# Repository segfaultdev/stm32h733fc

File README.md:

# STM32H733VGT6 Flight Controller

## Overview

This repository contains the hardware documentation and pinout routing for a custom flight controller based on the STM32H733VGT6 microcontroller. Designed for high-performance flight dynamics, this board leverages the MCU's 550 MHz clock speed, math coprocessor, and extensive I/O capabilities.

---

## Current Pinout & Peripheral Mapping

Below is the structured peripheral documentation based on the current schematic routing.

### 1. Serial Peripheral Interface (SPI)

*Primarily used for high-speed sensors (IMU), OSD chips, Blackbox Flash memory, and SD Cards.*

| Peripheral     | Pins              | Typical Signal Mapping                           | Suggested Use Case                                 |
| :------------- | :---------------- | :----------------------------------------------- | :------------------------------------------------- |
| **SPI1** | PA4 - PA7         | PA4 (NSS), PA5 (SCK), PA6 (MISO), PA7 (MOSI)     | **Primary IMU** (e.g., MPU6000, BMI270)      |
| **SPI2** | PB12 - PB15       | PB12 (NSS), PB13 (SCK), PB14 (MISO), PB15 (MOSI) | **Secondary IMU** or **OSD** (AT7456E) |
| **SPI3** | PA15, PC10 - PC12 | PA15 (NSS), PC10 (SCK), PC11 (MISO), PC12 (MOSI) | **Blackbox Flash** (e.g., W25Q128)           |
| **SPI4** | PE11 - PE14       | PE11 (NSS), PE12 (SCK), PE13 (MISO), PE14 (MOSI) | **SD Card** or **Third IMU**           |

### 2. Inter-Integrated Circuit (I2C)

*Used for slower, address-based peripherals like Barometers and Compasses.*

| Peripheral     | Pins        | Signal Mapping         | Suggested Use Case                             |
| :------------- | :---------- | :--------------------- | :--------------------------------------------- |
| **I2C1** | PB6 - PB7   | PB6 (SCL), PB7 (SDA)   | **Barometer** (e.g., BMP280, DPS310)     |
| **I2C2** | PB10 - PB11 | PB10 (SCL), PB11 (SDA) | **Magnetometer/Compass** (e.g., QMC5883) |
| **I2C4** | PD12 - PD13 | PD12 (SCL), PD13 (SDA) | Breakout / I2C Expansion Pad                   |

### 3. Universal Asynchronous Receiver-Transmitter (UART)

*Used for external communications: Radio Receivers, GPS, Digital Video Transmitters, and Telemetry.*

| Peripheral       | Pins        | Signal Mapping       | Suggested Use Case                                |
| :--------------- | :---------- | :------------------- | :------------------------------------------------ |
| **UART1**  | PA9 - PA10  | PA9 (TX), PA10 (RX)  | **Digital VTX** (DJI O3, Walksnail, HDZero) |
| **UART2**  | PA2 - PA3   | PA2 (TX), PA3 (RX)   | **Radio Receiver** (ExpressLRS / Crossfire) |
| **UART3**  | PD8 - PD9   | PD8 (TX), PD9 (RX)   | **GPS** (RX to GPS TX, TX to GPS RX)        |
| **UART4**  | PA0 - PA1   | PA0 (TX), PA1 (RX)   | **ESC Telemetry** (Usually RX only needed)  |
| **UART7**  | PE7 - PE8   | PE8 (TX), PE7 (RX)   | Free Serial Port                                  |
| **UART8**  | PE0 - PE1   | PE1 (TX), PE0 (RX)   | Free Serial Port                                  |
| **UART9**  | PD14 - PD15 | PD15 (TX), PD14 (RX) | Free Serial Port                                  |
| **UART10** | PE2 - PE3   | PE3 (TX), PE2 (RX)   | Free Serial Port                                  |

### 4. Controller Area Network (CAN)

*Used for robust, high-speed communication with DroneCAN peripherals (smart ESCs, advanced GPS modules).*

| Peripheral       | Pins      | Signal Mapping     | Suggested Use Case                |
| :--------------- | :-------- | :----------------- | :-------------------------------- |
| **FDCAN1** | PB8 - PB9 | PB9 (TX), PB8 (RX) | **DroneCAN Peripheral Bus** |

### 5. Timers & Motor Outputs

*Used for sending DSHOT or PWM signals to the Electronic Speed Controllers (ESCs).*

| Peripheral     | Pins      | Signal Mapping                             | Suggested Use Case                      |
| :------------- | :-------- | :----------------------------------------- | :-------------------------------------- |
| **TIM8** | PC6 - PC9 | PC6 (CH1), PC7 (CH2), PC8 (CH3), PC9 (CH4) | **Motor 1-4 Outputs** (DSHOT/PWM) |

---

## Hardware Routing To-Do List

The following critical subsystems still need to be established to make the flight controller fully functional.

- [ ] **USB Communication:** Route `PA11` (USB_D-) and `PA12` (USB_D+) and design the USB-C connector circuit with 5.1k CC pull-down resistors.
- [ ] **Debug and Flashing (SWD):** Route `PA13` (SWDIO) and `PA14` (SWCLK) to dedicated debug pads.
- [ ] **Analog Inputs (ADC):** Select ADC-capable pins (like `PC1`, `PC2`, or `PC3`) and route them to the Voltage Divider circuit (VBAT) and Current Sensor amplifier output.
- [ ] **System Basics:**
  - [ ] **Buzzer:** Route a GPIO pin to a transistor circuit for a 5V active buzzer.
  - [ ] **Status LEDs:** Route 1 or 2 free GPIO pins to drive status LEDs.
  - [ ] **Addressable LED Strip:** Route a DMA-capable timer pin for WS2812B RGB LEDs.

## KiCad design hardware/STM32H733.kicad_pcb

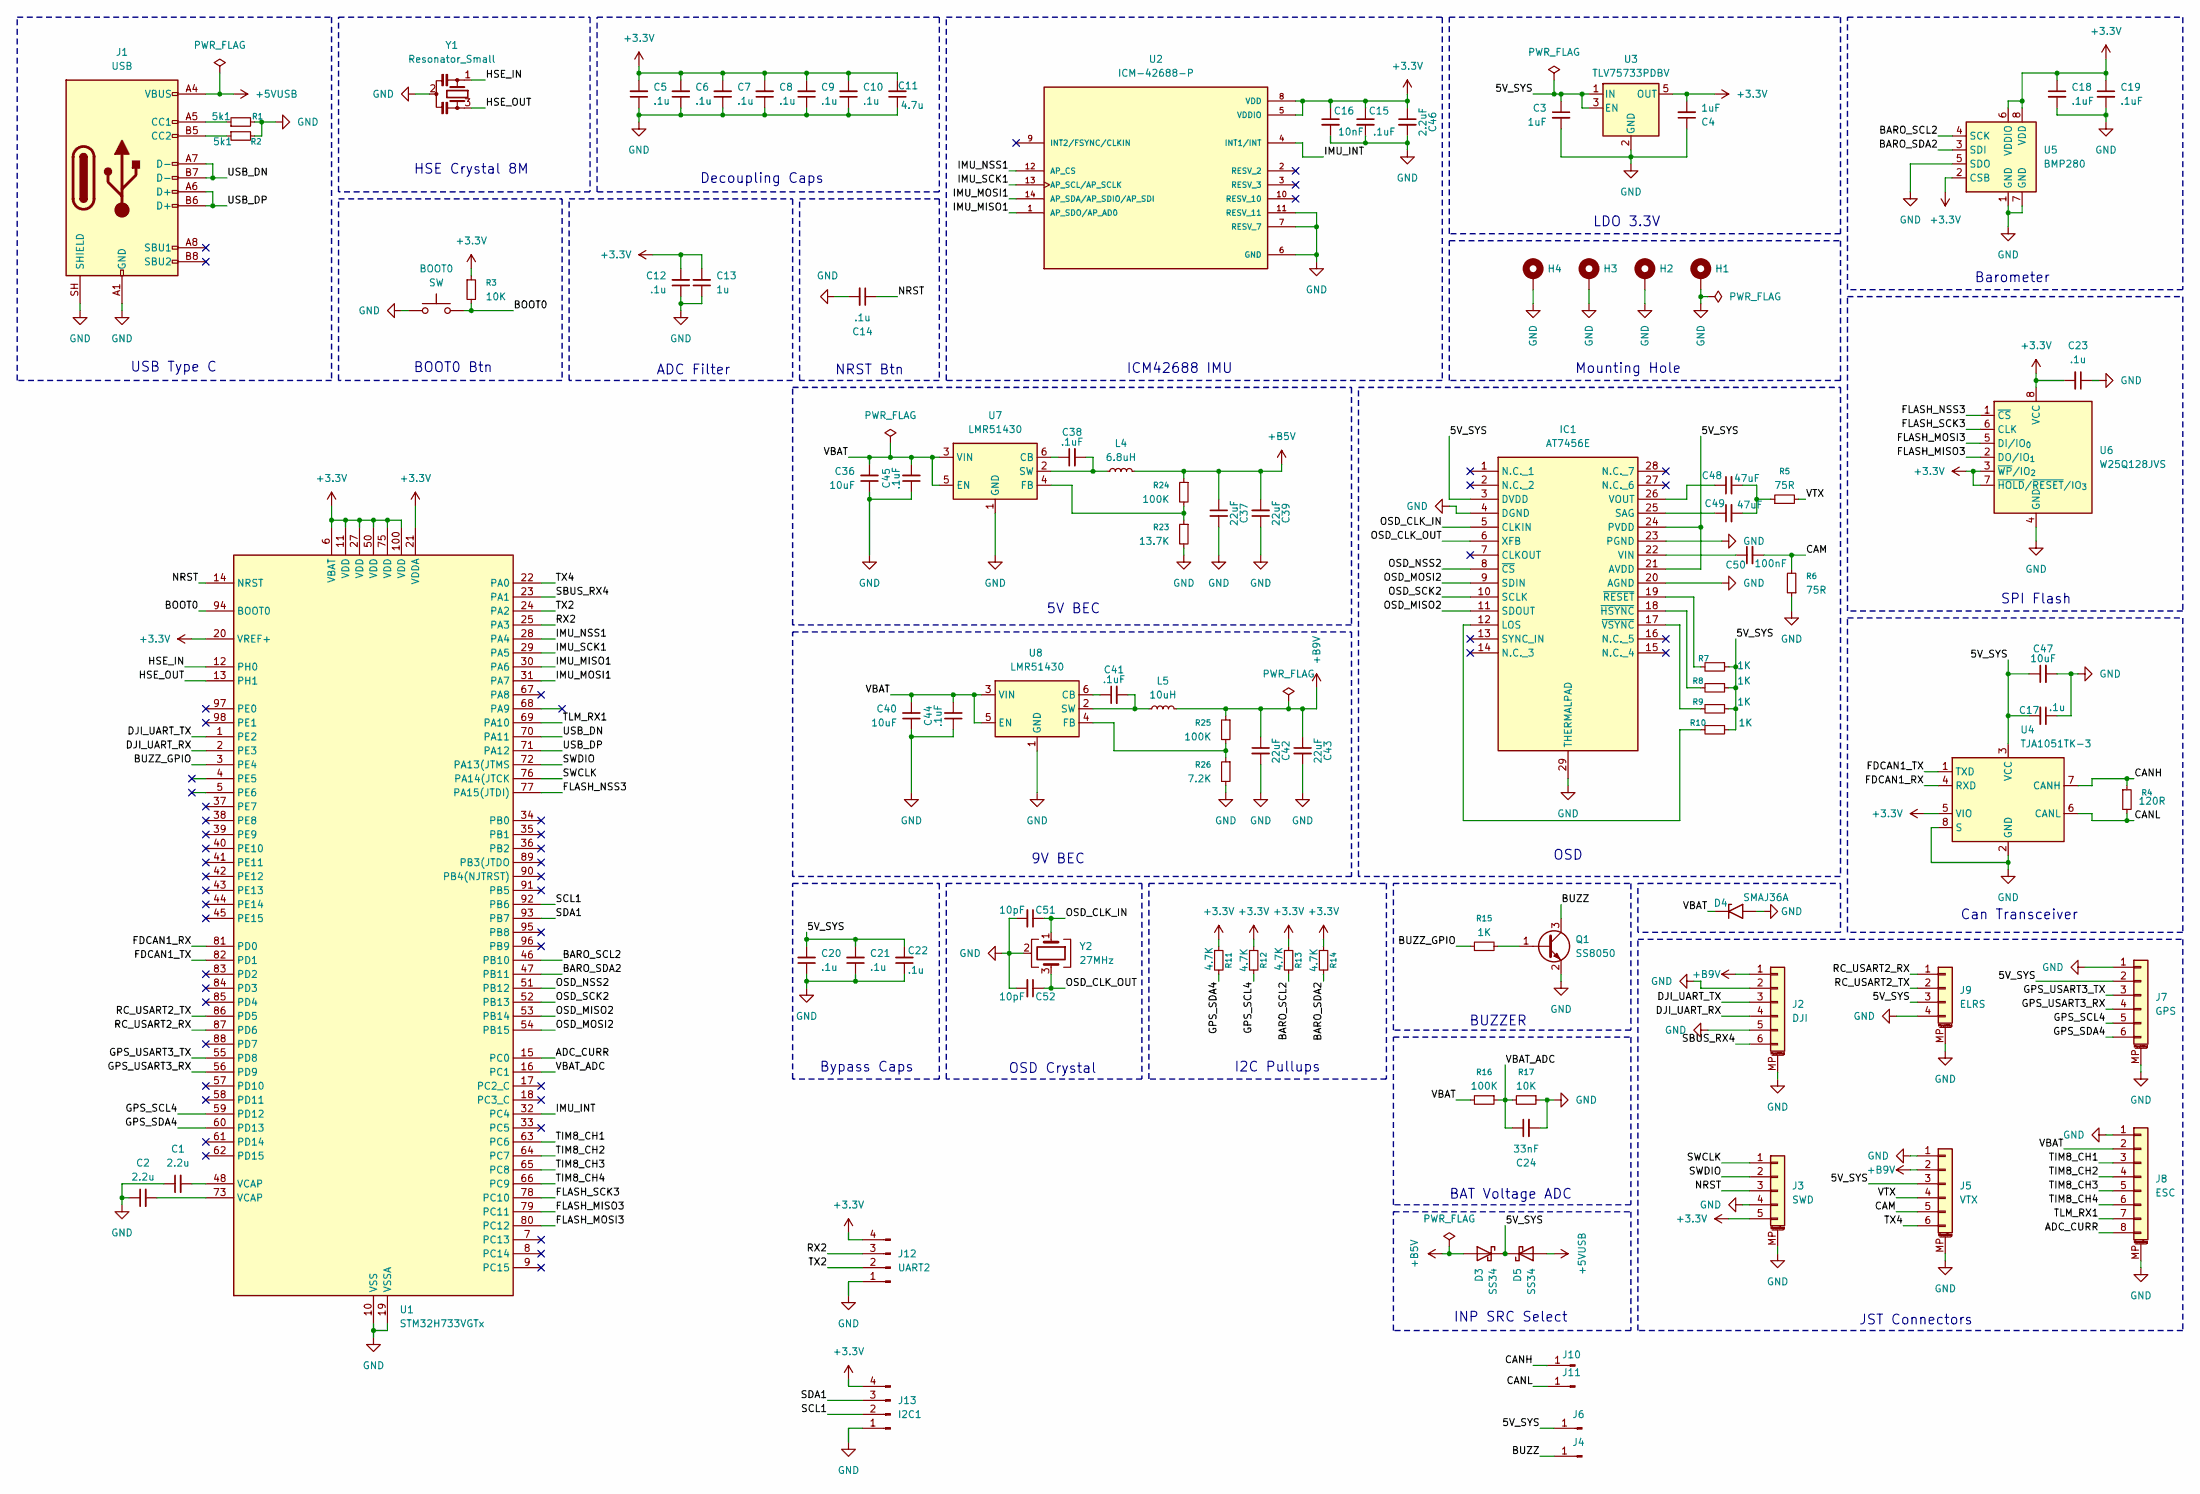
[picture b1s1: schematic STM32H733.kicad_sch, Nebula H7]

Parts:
BOOT0: SW; SW_Push_SPST_NO_Alps_SKRK
C1, C2: 2.2u; C_0402_1005Metric
C3, C4: 1uF; C_0603_1608Metric
C5, C6, C7, C8, C9, C10, C12, C14, C17, C20, C21, C22, C23: .1u; C_0402_1005Metric
C11: 4.7u; C_0603_1608Metric
C13: 1u; C_0402_1005Metric
C15, C18, C19: .1uF; C_0402_1005Metric
C16: 10nF; C_0402_1005Metric
C24: 33nF; C_0402_1005Metric
C36, C40, C47: 10uF; C_0805_2012Metric
C37, C39, C42, C43: 22uF; C_0805_2012Metric
C38, C41, C44, C45: .1uF; C_0603_1608Metric
C46: 2.2uF; C_0603_1608Metric
C48, C49: 47uF; CP_EIA-3216-18_Kemet-A
C50: 100nF; C_0402_1005Metric
C51, C52: 10pF; C_0402_1005Metric
D3, D5: SS34; D_SMA
D4: SMAJ36A; D_SMA
H1, H2, H3, H4: MountingHole_Pad; MountingHole_3.2mm_M3_Pad_Via
IC1: AT7456E; SOP65P640X120-29N; Manufacturer_Part_Number AT7456E
J1: USB; USB_C_Receptacle_GCT_USB4105-xx-A_16P_TopMnt_Horizontal
J2: DJI; JST_SH_SM06B-SRSS-TB_1x06-1MP_P1.00mm_Horizontal
J3: SWD; JST_SH_SM05B-SRSS-TB_1x05-1MP_P1.00mm_Horizontal
J4, J6: Conn_01x01_Pin; TestPoint_Pad_1.5x1.5mm
J5: VTX; JST_SH_SM06B-SRSS-TB_1x06-1MP_P1.00mm_Horizontal
J7: GPS; JST_SH_SM06B-SRSS-TB_1x06-1MP_P1.00mm_Horizontal
J8: ESC; JST_SH_SM08B-SRSS-TB_1x08-1MP_P1.00mm_Horizontal
J9: ELRS; JST_SH_SM04B-SRSS-TB_1x04-1MP_P1.00mm_Horizontal
J10: CH; TestPoint_Pad_1.0x1.0mm
J11: CL; TestPoint_Pad_1.0x1.0mm
J12: UART2; ConnPadx04
J13: I2C1; ConnPadx04
L4: 6.8uH; L_Changjiang_FXL0420
L5: 10uH; L_Changjiang_FXL0420
Q1: SS8050; SOT-23
R1, R2: 5k1; R_0402_1005Metric
R3, R17: 10K; R_0402_1005Metric
R4: 120R; R_0402_1005Metric
R5, R6: 75R; R_0402_1005Metric
R7, R8, R9, R10, R15: 1K; R_0402_1005Metric
R11, R12, R13, R14: 4.7K; R_0402_1005Metric
R16, R24, R25: 100K; R_0402_1005Metric
R23: 13.7K; R_0402_1005Metric
R26: 7.2K; R_0402_1005Metric
U1: STM32H733VGTx; LQFP-100_14x14mm_P0.5mm
U2: ICM-42688-P; PQFN50P300X250X97-14N; PARTREV 1.2
U3: TLV75733PDBV; SOT-23-5
U4: TJA1051TK-3; HVSON-8-1EP_3x3mm_P0.65mm_EP1.6x2.4mm
U5: BMP280; Bosch_LGA-8_2x2.5mm_P0.65mm_ClockwisePinNumbering
U6: W25Q128JVS; SOIC-8_5.3x5.3mm_P1.27mm
U7, U8: LMR51430; SOT-23-6
Y1: Resonator_Small; Resonator_SMD_Murata_CSTxExxV-3Pin_3.0x1.1mm
Y2: 27MHz; Crystal_SMD_3225-4Pin_3.2x2.5mm

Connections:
+3.3V: C4.2, C5.2, C6.2, C7.2, C8.2, C9.2, C10.2, C11.2, C12.2, C13.2, C15.1, C16.1, C18.1, C19.1, C23.2, C46.1, J3.5, J12.4, J13.4, R3.1, R11.1, R12.1, R13.1, R14.1, U1.6 (VBAT), U1.11 (VDD), U1.20 (VREF+), U1.21 (VDDA), U1.27 (VDD), U1.50 (VDD), U1.75 (VDD), U1.100 (VDD), U2.5 (VDDIO), U2.8 (VDD), U3.5 (OUT), U4.5 (VIO), U5.2 (CSB), U5.6 (VDDIO), U5.8 (VDD), U6.3 (~WP/IO_{2}), U6.7 (~HOLD/~RESET/IO_{3}), U6.8 (VCC)
+5VUSB: D5.2 (A), J1.A4 (VBUS), J1.A9 (VBUS), J1.B4 (VBUS), J1.B9 (VBUS)
+B5V: C37.1, C39.2, D3.2 (A), L4.2, R24.1
+B9V: C42.1, C43.1, J2.1, J5.2, L5.2, R25.1
/5V_SYS: C3.1, C17.2, C20.2, C21.2, C22.2, C47.1, D3.1 (K), D5.1 (K), IC1.3 (DVDD), IC1.21 (AVDD), IC1.24 (PVDD), J5.3, J6.1 (Pin_1_1), J7.2, J9.3, R7.1, R8.1, R9.1, R10.1, U3.1 (IN), U3.3 (EN), U4.3 (VCC)
/ADC_CURR: J8.8, U1.15 (PC0)
/BARO_SCL2: R13.2, U1.46 (PB10), U5.4 (SCK)
/BARO_SDA2: R14.2, U1.47 (PB11), U5.3 (SDI)
/BOOT0: BOOT0.2, R3.2, U1.94 (BOOT0)
/BUZZ: J4.1 (Pin_1_1), Q1.3 (C)
/BUZZ_GPIO: R15.1, U1.3 (PE4)
/CAM: C50.2, J5.5, R6.2
/CANH: J10.1 (Pin_1_1), R4.1, U4.7 (CANH)
/CANL: J11.1 (Pin_1_1), R4.2, U4.6 (CANL)
/DJI_UART_RX: J2.4, U1.2 (PE3)
/DJI_UART_TX: J2.3, U1.1 (PE2)
/FDCAN1_RX: U1.81 (PD0), U4.4 (RXD)
/FDCAN1_TX: U1.82 (PD1), U4.1 (TXD)
/FLASH_MISO3: U1.79 (PC11), U6.2 (DO/IO_{1})
/FLASH_MOSI3: U1.80 (PC12), U6.5 (DI/IO_{0})
/FLASH_NSS3: U1.77 (PA15(JTDI)), U6.1 (~CS)
/FLASH_SCK3: U1.78 (PC10), U6.6 (CLK)
/GPS_SCL4: J7.5, R12.2, U1.59 (PD12)
/GPS_SDA4: J7.6, R11.2, U1.60 (PD13)
/GPS_USART3_RX: J7.4, U1.56 (PD9)
/GPS_USART3_TX: J7.3, U1.55 (PD8)
/HSE_IN: U1.12 (PH0), Y1.1
/HSE_OUT: U1.13 (PH1), Y1.3
/IMU_INT: U1.32 (PC4), U2.4 (INT1/INT)
/IMU_MISO1: U1.30 (PA6), U2.1 (AP_SDO/AP_AD0)
/IMU_MOSI1: U1.31 (PA7), U2.14 (AP_SDA/AP_SDIO/AP_SDI)
/IMU_NSS1: U1.28 (PA4), U2.12 (AP_CS)
/IMU_SCK1: U1.29 (PA5), U2.13 (AP_SCL/AP_SCLK)
/NRST: C14.1, J3.3, U1.14 (NRST)
/OSD_CLK_IN: C51.1, IC1.5 (CLKIN), Y2.1
/OSD_CLK_OUT: C52.1, IC1.6 (XFB), Y2.3
/OSD_MISO2: IC1.11 (SDOUT), U1.53 (PB14)
/OSD_MOSI2: IC1.9 (SDIN), U1.54 (PB15)
/OSD_NSS2: IC1.8 (~CS), U1.51 (PB12)
/OSD_SCK2: IC1.10 (SCLK), U1.52 (PB13)
/RC_USART2_RX: J9.1, U1.87 (PD6)
/RC_USART2_TX: J9.2, U1.86 (PD5)
/RX2: J12.3, U1.25 (PA3)
/SBUS_RX4: J2.6, U1.23 (PA1)
/SCL1: J13.2, U1.92 (PB6)
/SDA1: J13.3, U1.93 (PB7)
/SWCLK: J3.1, U1.76 (PA14(JTCK)
/SWDIO: J3.2, U1.72 (PA13(JTMS)
/TIM8_CH1: J8.3, U1.63 (PC6)
/TIM8_CH2: J8.4, U1.64 (PC7)
/TIM8_CH3: J8.5, U1.65 (PC8)
/TIM8_CH4: J8.6, U1.66 (PC9)
/TLM_RX1: J8.7, U1.69 (PA10)
/TX1: U1.68 (PA9)
/TX2: J12.2, U1.24 (PA2)
/TX4: J5.6, U1.22 (PA0)
/USB_DN: J1.A7 (D-), J1.B7 (D-), U1.70 (PA11)
/USB_DP: J1.A6 (D+), J1.B6 (D+), U1.71 (PA12)
/VBAT: C36.2, C40.2, C44.2, C45.2, D4.1 (A1), J8.2, R16.2, U7.3 (VIN), U7.5 (EN), U8.3 (VIN), U8.5 (EN)
/VBAT_ADC: C24.1, R16.1, R17.2, U1.16 (PC1)
/VTX: J5.4, R5.2
GND: BOOT0.1, C1.1, C2.1, C3.2, C4.1, C5.1, C6.1, C7.1, C8.1, C9.1, C10.1, C11.1, C12.1, C13.1, C14.2, C15.2, C16.2, C17.1, C18.2, C19.2, C20.1, C21.1, C22.1, C23.1, C24.2, C36.1, C37.2, C39.1, C40.1, C42.2, C43.2, C44.1, C45.1, C46.2, C47.2, C51.2, C52.2, D4.2 (A2), H1.1 (1_1), H2.1 (1_1), H3.1 (1_1), H4.1 (1_1), IC1.4 (DGND), IC1.20 (AGND), IC1.23 (PGND), IC1.29 (THERMALPAD), J1.A1 (GND), J1.A12 (GND), J1.B1 (GND), J1.B12 (GND), J1.SH (SHIELD), J2.2, J2.5, J2.MP (MountPin), J3.4, J3.MP (MountPin), J5.1, J5.MP (MountPin), J7.1, J7.MP (MountPin), J8.1, J8.MP (MountPin), J9.4, J9.MP (MountPin), J12.1, J13.1, Q1.2 (E), R1.2, R2.2, R6.1, R17.1, R23.2, R26.2, U1.10 (VSS), U1.19 (VSSA), U1.26 (VSS), U1.49 (VSS), U1.74 (VSS), U1.99 (VSS), U2.6 (GND), U2.7 (RESV_7), U2.11 (RESV_11), U3.2 (GND), U4.2 (GND), U4.8 (S), U4.9 (GND), U5.1 (GND), U5.5 (SDO), U5.7 (GND), U6.4 (GND), U7.1 (GND), U8.1 (GND), Y1.2, Y2.2 (G), Y2.4 (G)
unnamed: C1.2, U1.48 (VCAP)
unnamed: C2.2, U1.73 (VCAP)
unnamed: C48.2, C49.2, R5.1
unnamed: IC1.12 (LOS), R10.2
unnamed: C49.1, IC1.25 (SAG)
unnamed: C50.1, IC1.22 (VIN)
unnamed: C48.1, IC1.26 (VOUT)
unnamed: IC1.18 (~HSYNC), R8.2
unnamed: IC1.19 (~RESET), R7.2
unnamed: IC1.17 (~VSYNC), R9.2
unnamed: J1.A5 (CC1), R1.1
unnamed: J1.B5 (CC2), R2.1
unnamed: Q1.1 (B), R15.2
unnamed: C38.1, U7.6 (CB)
unnamed: R23.1, R24.2, U7.4 (FB)
unnamed: C38.2, L4.1, U7.2 (SW)
unnamed: C41.1, U8.6 (CB)
unnamed: R25.2, R26.1, U8.4 (FB)
unnamed: C41.2, L5.1, U8.2 (SW)

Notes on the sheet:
HSE Crystal 8M
Can Transceiver
INP SRC Select
OSD
SPI Flash
BUZZER
ICM42688 IMU
NRST Btn
Bypass Caps
ADC Filter
USB Type C
Barometer
5V BEC
I2C Pullups
BAT Voltage ADC
Decoupling Caps
OSD Crystal
9V BEC
LDO 3.3V
JST Connectors
Mounting Hole
BOOT0 Btn

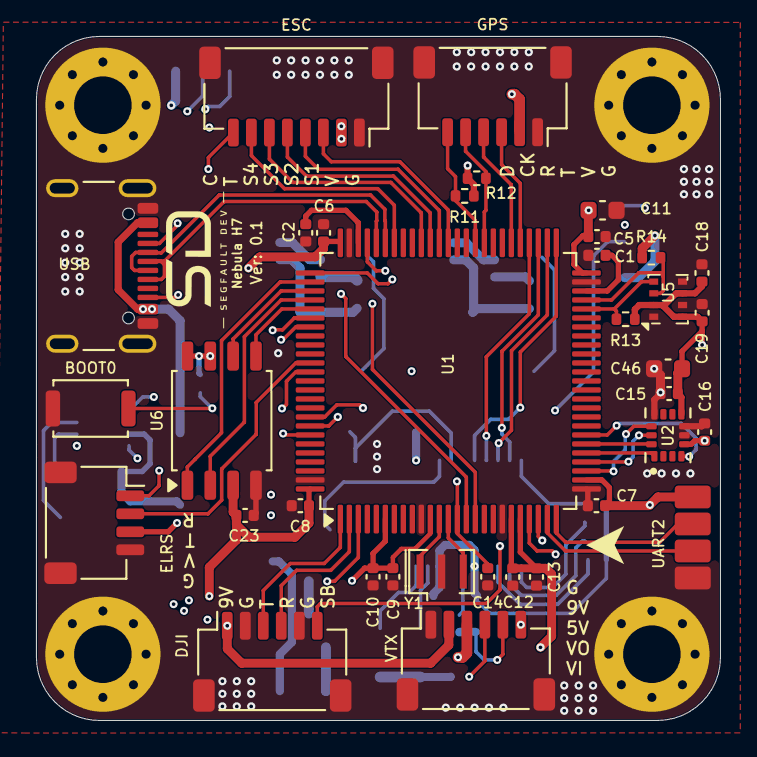
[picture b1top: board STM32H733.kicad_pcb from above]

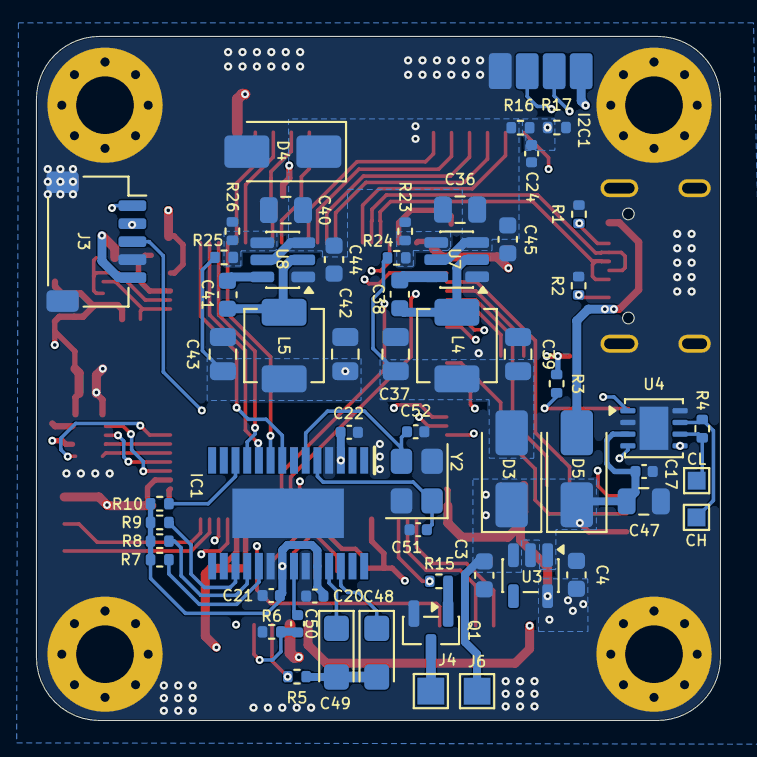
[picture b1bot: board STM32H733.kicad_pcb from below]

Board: 4 copper layers, 38.0 x 38.0 mm, 97 parts (58 on the bottom side), 80 nets.

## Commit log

2026-05-06 H733 flight controller first commit
2026-05-10 New Layout designed
2026-05-12 New Directory Structure
2026-05-12 Mostly Done. Need to Fix some Warnings, Need to add Soldering Pad for
    CANH and CANL, need to add few pads for UART, I2C, SPI for future use
    Need some Test Pads for power
2026-05-13 Flight Controller:
    Almost Done With the PCB design Except the Leds
    and Few Peripherals Pad for external Sensors
    and modules
2026-05-14 Nebula H7: V 0.1
    need to add some indicator led
